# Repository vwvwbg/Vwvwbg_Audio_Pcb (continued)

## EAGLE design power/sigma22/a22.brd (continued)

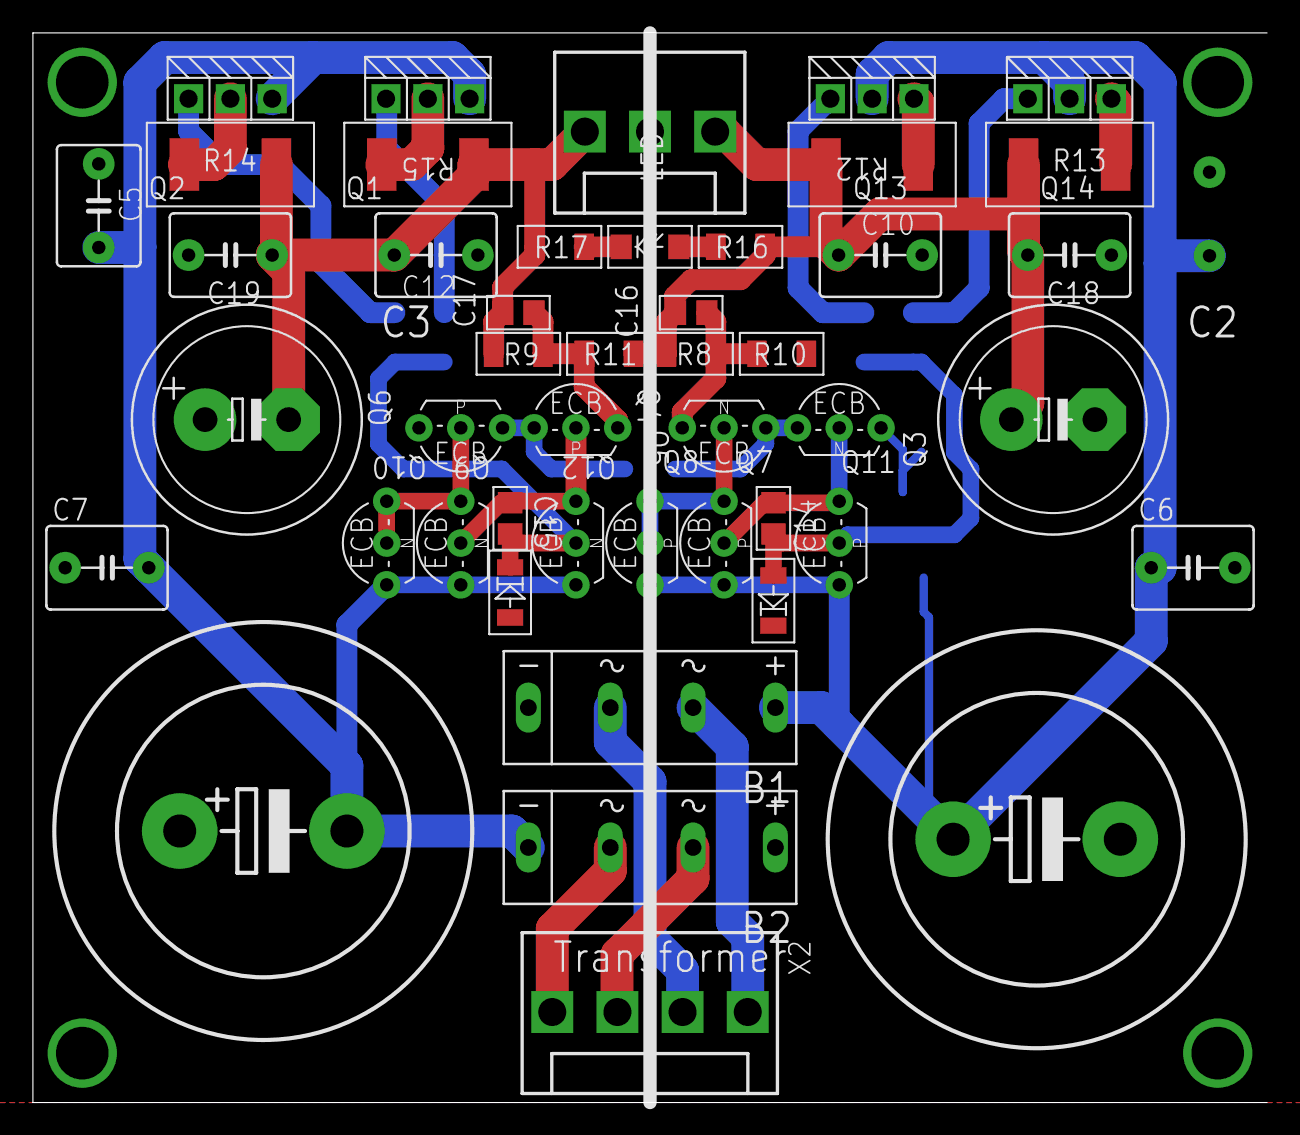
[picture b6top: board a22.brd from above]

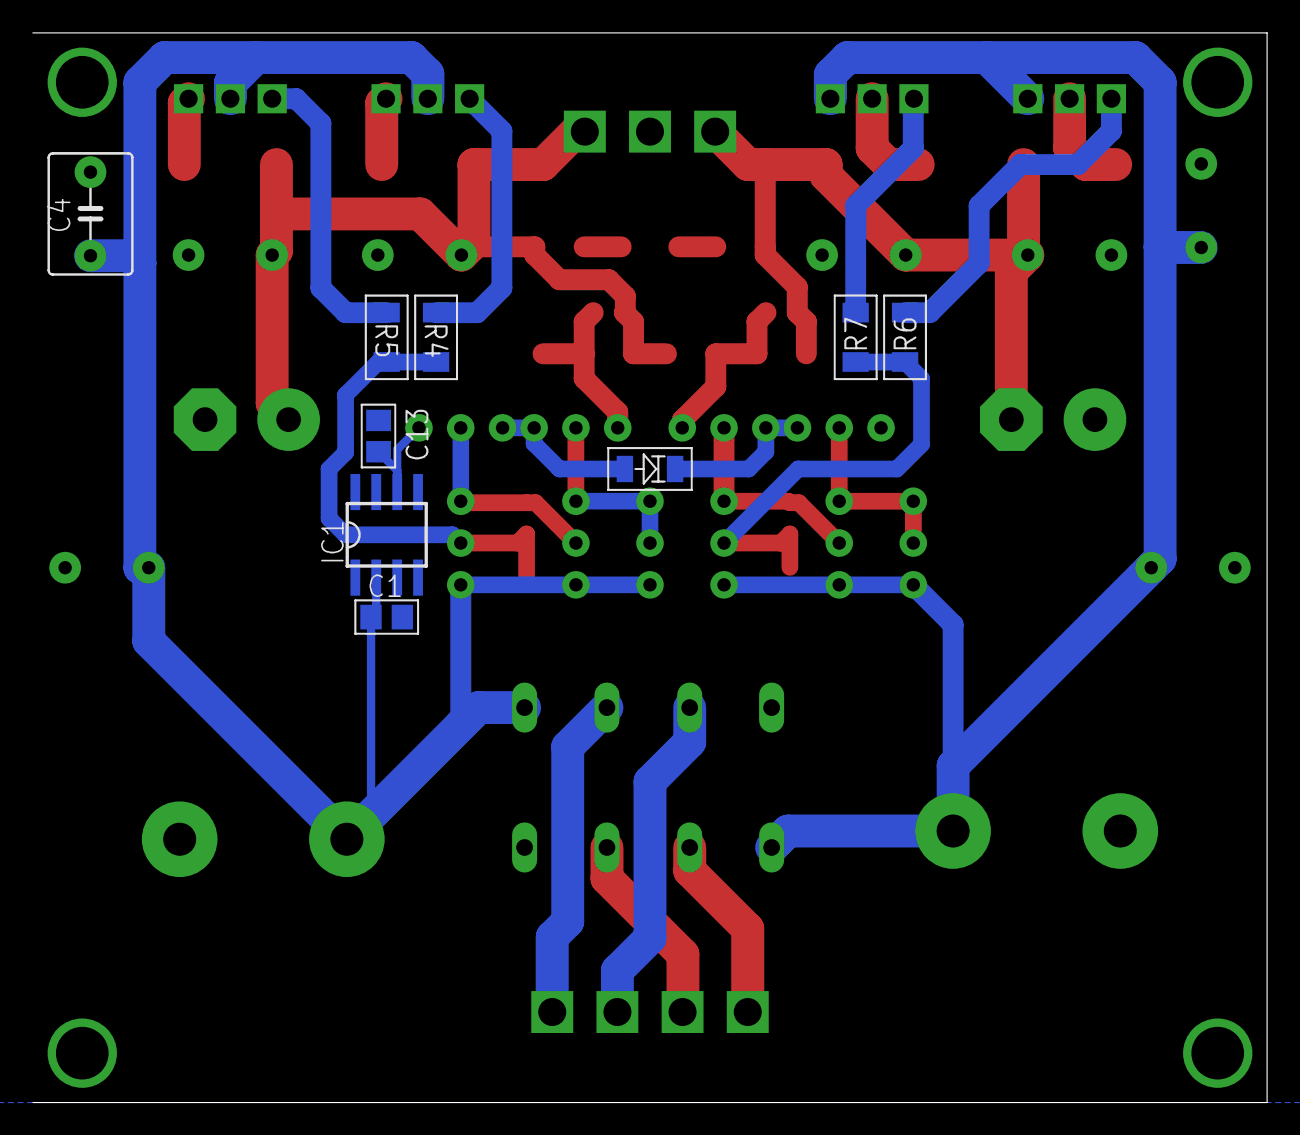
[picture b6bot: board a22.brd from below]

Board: 2 copper layers, 75.0 x 65.0 mm, 59 parts (9 on the bottom side), 30 nets.

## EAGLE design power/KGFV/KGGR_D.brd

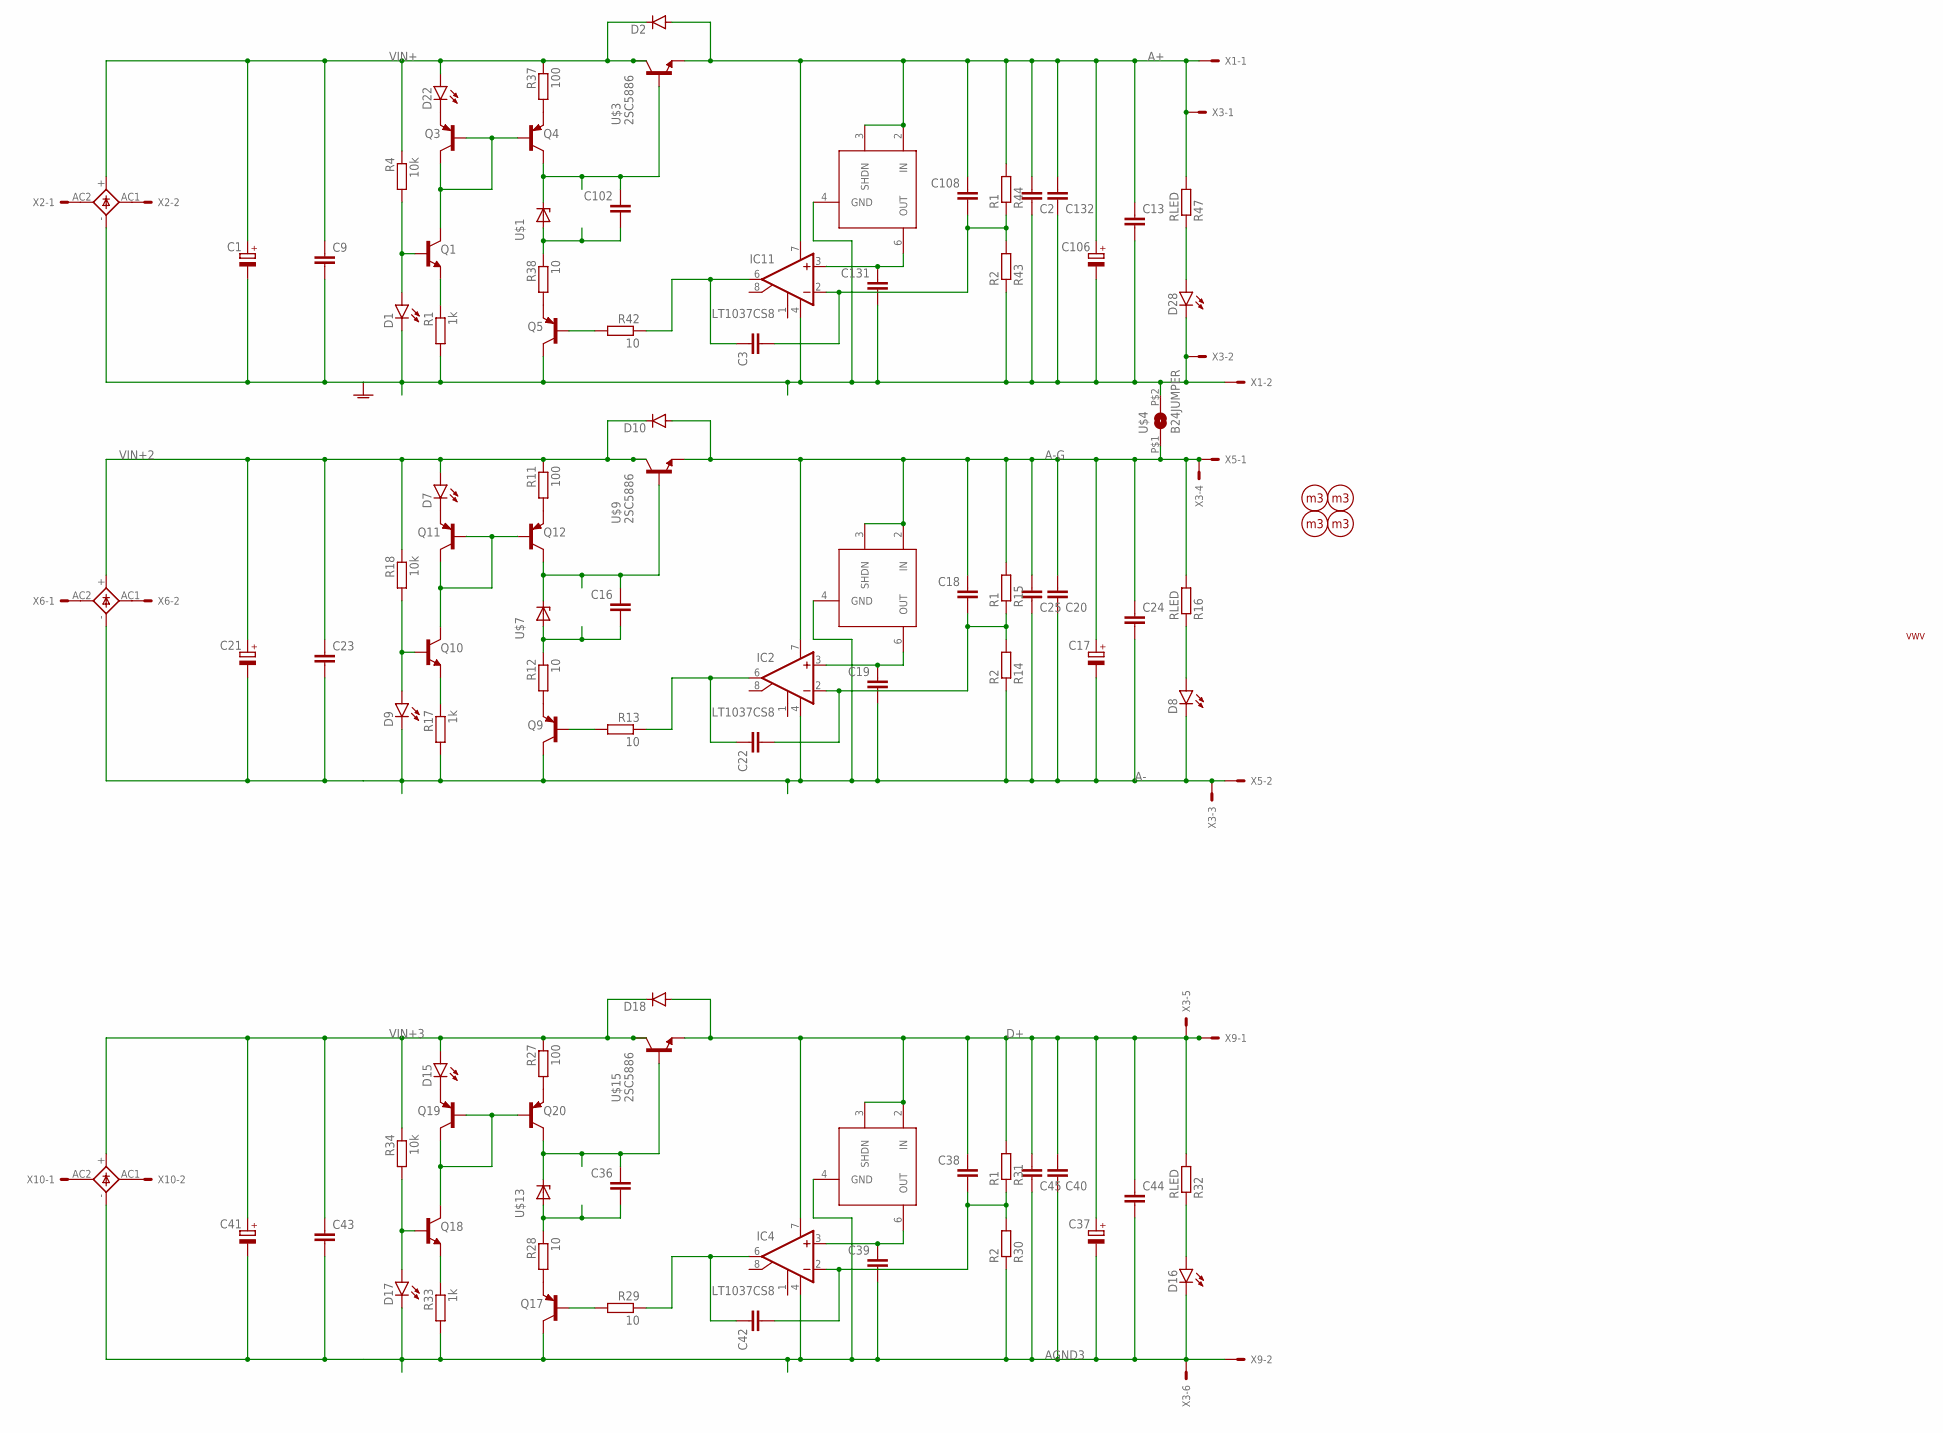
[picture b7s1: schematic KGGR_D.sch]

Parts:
B1, B3, B5: GBU4; GBU4S
C1, C21, C41: CPOL-EUE7.5-18; E7,5-18
C2, C3, C16, C18, C20, C22, C25, C36, C38, C40, C42, C45, C102, C108, C132: C-EUC0805; C0805
C9, C13, C23, C24, C43, C44: C-EU050-050X075; C050-050X075
C17, C37, C106: CPOL-EUE5-10.5; E5-10,5
C19, C39, C131: C-EUC1206; C1206
D1, D7, D8, D9, D15, D16, D17, D22, D28: LEDVWV1206; LED_SML1206
D2, D10, D18: DIODE-DO214AC; DO214AC
H1, H2, H3, H4: HOLE; M3_HOLE
IC2, IC4, IC11: LT1037CS8; SOIC8
Q1, Q10, Q18: TRANSISTOR_BC847CLT1-NPN-SOT23-BEC; TRANSISTOR_SOT23-BEC
Q3, Q4, Q5, Q9, Q11, Q12, Q17, Q19, Q20: TRANSISTOR_BC857C-PNP-SOT23-BEC; TRANSISTOR_SOT23-BEC
R1, R17, R33: 1k; MINI_MELF-0204W
R4, R18, R34: 10k; MINI_MELF-0204W
R11, R27, R37: 100; MINI_MELF-0204W
R12, R13, R28, R29, R38, R42: 10; MINI_MELF-0204W
R14, R30, R43: R2; MINI_MELF-0204W
R15, R31, R44: R1; MINI_MELF-0204W
R16, R32, R47: RLED; MINI_MELF-0204W
S1: VWV
U$1, U$7, U$13: ADR504X; SOT-23
U$2, U$8, U$14: LT6657; MSOP8
U$3, U$9, U$15: 2SC5886; NEW-PWMOLD
U$4: B24JUMPER; B24J
X1, X2, X5, X6, X9, X10: KK-156-2
X3: KK-156-6

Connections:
A+: C2.2, C13.1, C106.+, C108.1, C132.2, D2.A, IC11.7 (V+), R44.2, R47.2, U$2.2 (IN), U$2.3 (SHDN), U$3.3 (E), X1.1, X3.1
A-: B3.-, C17.-, C19.2, C20.1, C21.-, C23.2, C24.2, C25.1, D8.C, D9.C, IC2.4 (V-), Q9.C, R14.1, R17.2, U$8.4 (GND), X3.3, X5.2
A-G: C17.+, C18.1, C20.2, C24.1, C25.2, D10.A, IC2.7 (V+), R15.2, R16.2, U$4.P$1 (1), U$8.2 (IN), U$8.3 (SHDN), U$9.3 (E), X3.4, X5.1
AGND: B1.-, C1.-, C2.1, C9.2, C13.2, C106.-, C131.2, C132.1, D1.C, D28.C, IC11.4 (V-), Q5.C, R1.2, R43.1, U$2.4 (GND), U$4.P$2 (2), X1.2, X3.2
AGND3: B5.-, C37.-, C39.2, C40.1, C41.-, C43.2, C44.2, C45.1, D16.C, D17.C, IC4.4 (V-), Q17.C, R30.1, R33.2, U$14.4 (GND), X3.6, X9.2
D+: C37.+, C38.1, C40.2, C44.1, C45.2, D18.A, IC4.7 (V+), R31.2, R32.2, U$14.2 (IN), U$14.3 (SHDN), U$15.3 (E), X3.5, X9.1
unnamed: C102.1, Q4.C, U$1.1 (OUT), U$3.1 (B)
unnamed: D22.C, Q3.E
unnamed: Q4.E, R37.2
unnamed: B1.AC1 (AC2), X2.2
unnamed: B1.AC2 (AC1), X2.1
unnamed: Q1.E, R1.1
unnamed: D1.A, Q1.B, R4.2
unnamed: Q10.C, Q11.B, Q11.C, Q12.B
unnamed: C16.2, R12.1, U$7.2 (GND)
unnamed: Q9.E, R12.2
unnamed: Q9.B, R13.2
unnamed: C18.2, C22.2, IC2.2 (-IN), R14.2, R15.1
unnamed: D8.A, R16.1
unnamed: C19.1, IC2.3 (+IN), U$8.6 (OUT)
unnamed: C22.1, IC2.6 (OUT), R13.1
unnamed: Q10.E, R17.1
unnamed: D9.A, Q10.B, R18.2
unnamed: C16.1, Q12.C, U$7.1 (OUT), U$9.1 (B)
unnamed: D7.C, Q11.E
unnamed: Q12.E, R11.2
unnamed: B3.AC1 (AC2), X6.2
unnamed: B3.AC2 (AC1), X6.1
unnamed: Q18.C, Q19.B, Q19.C, Q20.B
unnamed: C36.2, R28.1, U$13.2 (GND)
unnamed: Q17.E, R28.2
unnamed: Q17.B, R29.2
unnamed: C38.2, C42.2, IC4.2 (-IN), R30.2, R31.1
unnamed: D16.A, R32.1
unnamed: C39.1, IC4.3 (+IN), U$14.6 (OUT)
unnamed: C42.1, IC4.6 (OUT), R29.1
unnamed: Q18.E, R33.1
unnamed: D17.A, Q18.B, R34.2
unnamed: C36.1, Q20.C, U$13.1 (OUT), U$15.1 (B)
unnamed: D15.C, Q19.E
unnamed: Q20.E, R27.2
unnamed: B5.AC1 (AC2), X10.2
unnamed: B5.AC2 (AC1), X10.1
unnamed: Q1.C, Q3.B, Q3.C, Q4.B
unnamed: C102.2, R38.1, U$1.2 (GND)
unnamed: Q5.E, R38.2
unnamed: Q5.B, R42.2
unnamed: C3.2, C108.2, IC11.2 (-IN), R43.2, R44.1
unnamed: D28.A, R47.1
unnamed: C131.1, IC11.3 (+IN), U$2.6 (OUT)
unnamed: C3.1, IC11.6 (OUT), R42.1
VIN+: B1.+, C1.+, C9.1, D2.C, D22.A, R4.1, R37.1, U$3.2 (C), U$3.4 (C), U$3.P$1 (C), U$3.P$2 (C), U$3.P$3 (C), U$3.P$4 (C), U$3.P$5 (C), U$3.P$6 (C), U$3.P$7 (C), U$3.P$8 (C), U$3.P$9 (C), U$3.P$10 (C), U$3.P$11 (C), U$3.P$12 (C), U$3.P$13 (C), U$3.P$14 (C), U$3.P$15 (C), U$3.P$16 (C), U$3.P$17 (C), U$3.P$18 (C), U$3.P$19 (C), U$3.P$20 (C), U$3.P$21 (C), U$3.P$22 (C), U$3.P$23 (C), U$3.P$24 (C), U$3.P$25 (C), U$3.P$26 (C), U$3.P$27 (C), U$3.P$28 (C), U$3.P$29 (C), U$3.P$30 (C), U$3.P$31 (C), U$3.P$32 (C), U$3.P$33 (C), U$3.P$34 (C), U$3.P$35 (C), U$3.P$36 (C), U$3.P$37 (C), U$3.P$38 (C), U$3.P$39 (C), U$3.P$40 (C), U$3.P$41 (C), U$3.P$42 (C), U$3.P$43 (C), U$3.P$44 (C), U$3.P$45 (C), U$3.P$46 (C), U$3.P$47 (C), U$3.P$48 (C), U$3.P$49 (C), U$3.P$50 (C), U$3.P$51 (C), U$3.P$52 (C), U$3.P$53 (C), U$3.P$54 (C), U$3.P$55 (C), U$3.P$56 (C), U$3.P$57 (C), U$3.P$58 (C), U$3.P$59 (C), U$3.P$60 (C), U$3.P$61 (C), U$3.P$62 (C), U$3.P$63 (C)
VIN+2: B3.+, C21.+, C23.1, D7.A, D10.C, R11.1, R18.1, U$9.2 (C), U$9.4 (C), U$9.P$1 (C), U$9.P$2 (C), U$9.P$3 (C), U$9.P$4 (C), U$9.P$5 (C), U$9.P$6 (C), U$9.P$7 (C), U$9.P$8 (C), U$9.P$9 (C), U$9.P$10 (C), U$9.P$11 (C), U$9.P$12 (C), U$9.P$13 (C), U$9.P$14 (C), U$9.P$15 (C), U$9.P$16 (C), U$9.P$17 (C), U$9.P$18 (C), U$9.P$19 (C), U$9.P$20 (C), U$9.P$21 (C), U$9.P$22 (C), U$9.P$23 (C), U$9.P$24 (C), U$9.P$25 (C), U$9.P$26 (C), U$9.P$27 (C), U$9.P$28 (C), U$9.P$29 (C), U$9.P$30 (C), U$9.P$31 (C), U$9.P$32 (C), U$9.P$33 (C), U$9.P$34 (C), U$9.P$35 (C), U$9.P$36 (C), U$9.P$37 (C), U$9.P$38 (C), U$9.P$39 (C), U$9.P$40 (C), U$9.P$41 (C), U$9.P$42 (C), U$9.P$43 (C), U$9.P$44 (C), U$9.P$45 (C), U$9.P$46 (C), U$9.P$47 (C), U$9.P$48 (C), U$9.P$49 (C), U$9.P$50 (C), U$9.P$51 (C), U$9.P$52 (C), U$9.P$53 (C), U$9.P$54 (C), U$9.P$55 (C), U$9.P$56 (C), U$9.P$57 (C), U$9.P$58 (C), U$9.P$59 (C), U$9.P$60 (C), U$9.P$61 (C), U$9.P$62 (C), U$9.P$63 (C)
VIN+3: B5.+, C41.+, C43.1, D15.A, D18.C, R27.1, R34.1, U$15.2 (C), U$15.4 (C), U$15.P$1 (C), U$15.P$2 (C), U$15.P$3 (C), U$15.P$4 (C), U$15.P$5 (C), U$15.P$6 (C), U$15.P$7 (C), U$15.P$8 (C), U$15.P$9 (C), U$15.P$10 (C), U$15.P$11 (C), U$15.P$12 (C), U$15.P$13 (C), U$15.P$14 (C), U$15.P$15 (C), U$15.P$16 (C), U$15.P$17 (C), U$15.P$18 (C), U$15.P$19 (C), U$15.P$20 (C), U$15.P$21 (C), U$15.P$22 (C), U$15.P$23 (C), U$15.P$24 (C), U$15.P$25 (C), U$15.P$26 (C), U$15.P$27 (C), U$15.P$28 (C), U$15.P$29 (C), U$15.P$30 (C), U$15.P$31 (C), U$15.P$32 (C), U$15.P$33 (C), U$15.P$34 (C), U$15.P$35 (C), U$15.P$36 (C), U$15.P$37 (C), U$15.P$38 (C), U$15.P$39 (C), U$15.P$40 (C), U$15.P$41 (C), U$15.P$42 (C), U$15.P$43 (C), U$15.P$44 (C), U$15.P$45 (C), U$15.P$46 (C), U$15.P$47 (C), U$15.P$48 (C), U$15.P$49 (C), U$15.P$50 (C), U$15.P$51 (C), U$15.P$52 (C), U$15.P$53 (C), U$15.P$54 (C), U$15.P$55 (C), U$15.P$56 (C), U$15.P$57 (C), U$15.P$58 (C), U$15.P$59 (C), U$15.P$60 (C), U$15.P$61 (C), U$15.P$62 (C), U$15.P$63 (C)

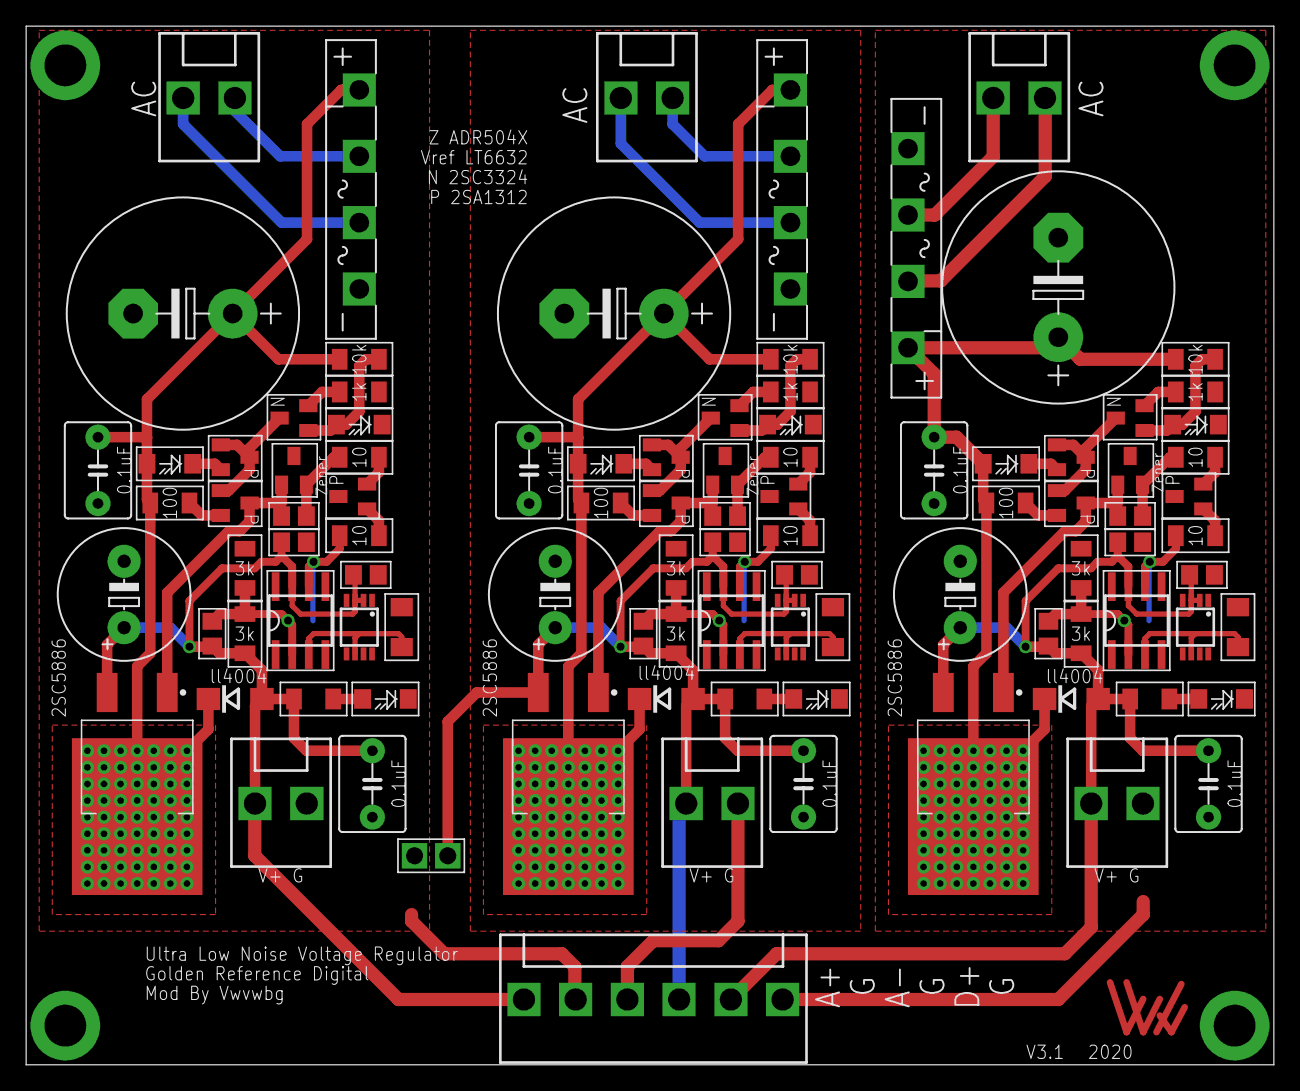
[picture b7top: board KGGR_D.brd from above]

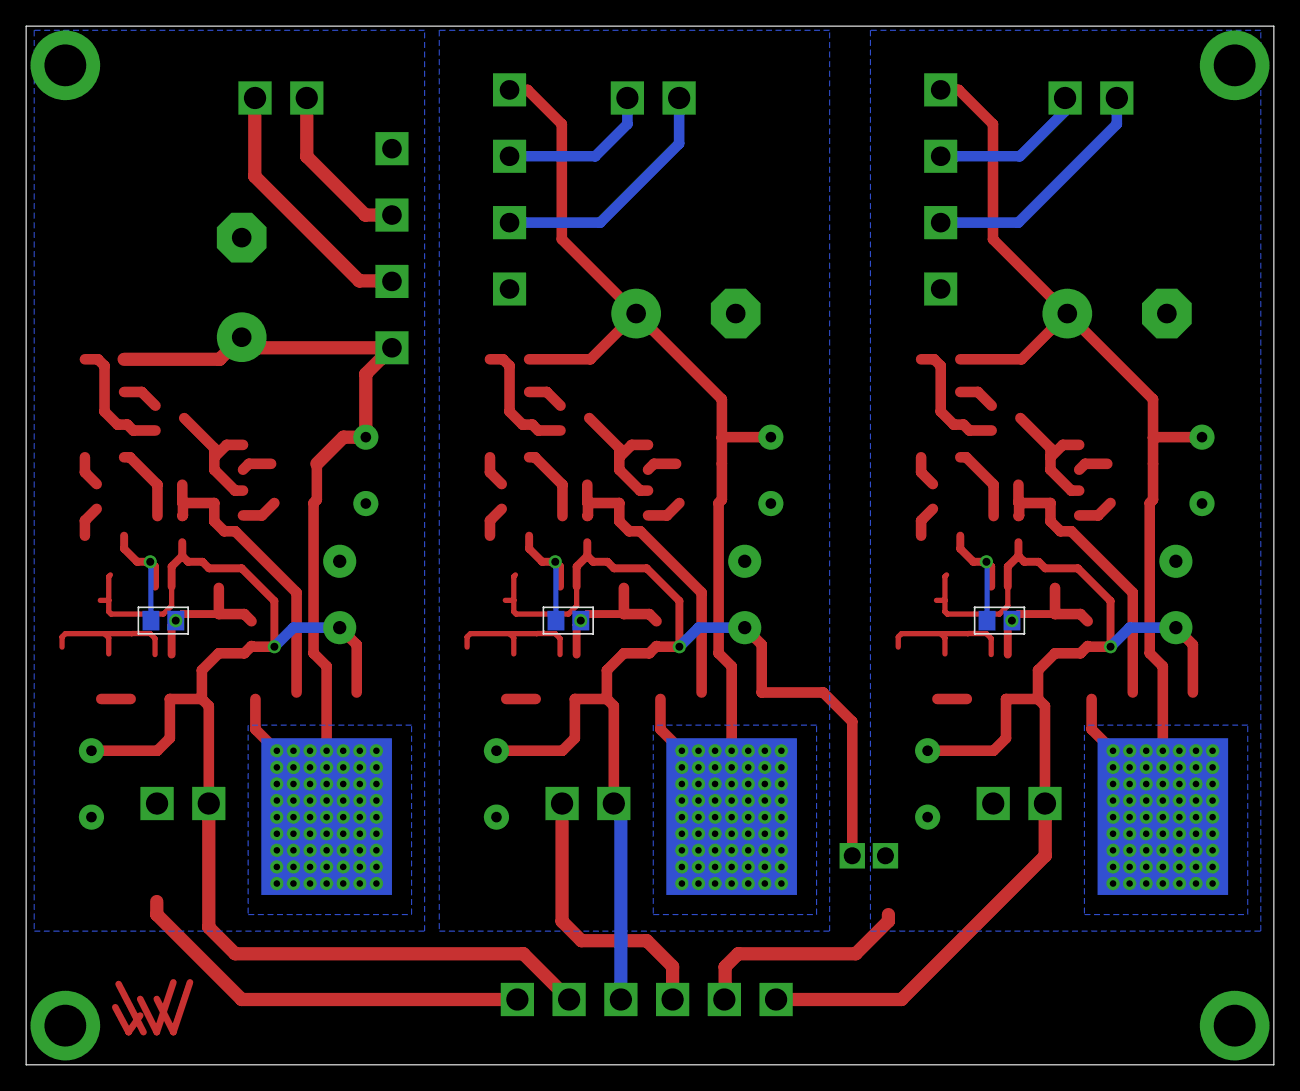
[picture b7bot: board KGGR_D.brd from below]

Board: 2 copper layers, 95.5 x 79.5 mm, 106 parts (3 on the bottom side), 54 nets.

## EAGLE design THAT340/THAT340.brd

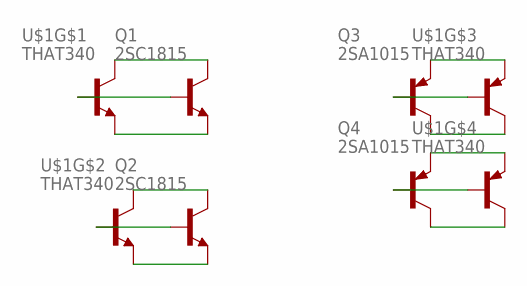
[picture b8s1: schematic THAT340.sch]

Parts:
Q1, Q2: 2SC1815; TO92-BCE
Q3, Q4: 2SA1015; TO92-BCE
U$1: THAT340; DIP254P762X510-14

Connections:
unnamed: Q1.C, U$1.1 (C)
unnamed: Q1.B, U$1.2 (B)
unnamed: Q1.E, U$1.3 (E)
unnamed: Q2.C, U$1.14 (C)
unnamed: Q2.B, U$1.13 (B)
unnamed: Q2.E, U$1.12 (E)
unnamed: Q4.E, U$1.10 (E)
unnamed: Q3.C, U$1.7 (C)
unnamed: Q3.B, U$1.6 (B)
unnamed: Q3.E, U$1.5 (E)
unnamed: Q4.B, U$1.9 (B)
unnamed: Q4.C, U$1.8 (C)

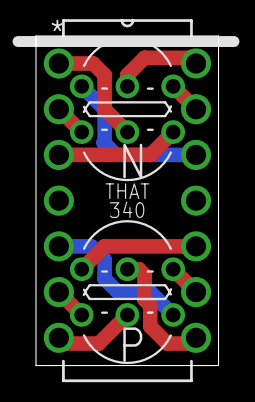
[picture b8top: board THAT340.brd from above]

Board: 2 copper layers, 10.1 x 18.3 mm, 5 parts (0 on the bottom side), 12 nets.

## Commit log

2020-03-08 gitignore setup
2020-03-08 first clone to github
2020-03-08 Readme
2020-03-17 dynalo_smd_mod update
2020-03-17 add some project
2020-03-17 add more project
2020-06-19 VCFA2
2020-07-04 0703
2020-08-25 VCFA V3
